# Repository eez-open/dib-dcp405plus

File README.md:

### This is a WORK IN PROGRESS!

---

### Ownership and License
The contributors are listed in CONTRIB.TXT. 

Licenses | OSHWA UID
--|--
 | 

### Overview

The EEZ DIB DCP405+ Power module is an improved version of the [DCP405](https://github.com/eez-open/modular-psu/tree/master/dcp405) module that now includes an on-board 32-bit MCU, a more accurate and faster A/D converter for simultaneous voltage and current measurement (and thus more accurate power measurement).
This version features remote current programming in addition to the existing remote voltage programming. Sense inputs are also on 4 mm safety sockets, which now enables usage of widely available (e.g. AliExpress, eBay, etc.) and affordable Kelvin cable sets (Power/Sense) usually used with LCR meters (see below)

### Feature list
- Power input: 48 Vdc (e.g. Mean Well EPP-150-48 or LRS-150F-48)
- Max. output power: 155 W (as limited with Mean Well AC/DC module capacity) 
- Voltage regulation (CV), 0 – 40 V. Voltage set resolution (_U_SET_): 16-bit, read resolution (_U_MON_): 15-bit
- Current regulation (CC) with 2-range (50 mA, 5 A). Current set resolution (_I_SET_): 16-bit, Current read resolution (_I_MON_): 20-bit for each range
- On-board low EMI switching power pre-regulator and bias power supply
- On-board OVP with full range dual crowbar (triac/MOSFET) and 20x5 mm fuse
- Down-programmer
- Output enable (OE) circuit with LED indicator combined with coupling indication
- Ø4 mm sockets (19.05 mm/0.75” pitch) for Power outputs and Sense inputs 
- Pass-thru connector for power output coupling with other power boards for e.g. doubling output voltage (up to 80 V) or current (up to 10 A)
- Remote voltage sense with LED indicator and inverse polarity protection
- Remote voltage and current programming with LED indicator (+2.5 V for full range)
- On-board 32-bit 250 MHz MCU ([STM32H503CBT6](https://www.st.com/en/microcontrollers-microprocessors/stm32h503cb.html))
- Galvanically isolated SPI bus
- I2C EEPROM for storing board specific configuration and calibration parameters
- SPI Temperature sensor
- Dimensions: 180 x 103.5 mm, 4-layer PCB
- **CE certified design**

---

This work is financed by [NLnet](https://nlnet.nl/project/BB3-CM5/) foundation

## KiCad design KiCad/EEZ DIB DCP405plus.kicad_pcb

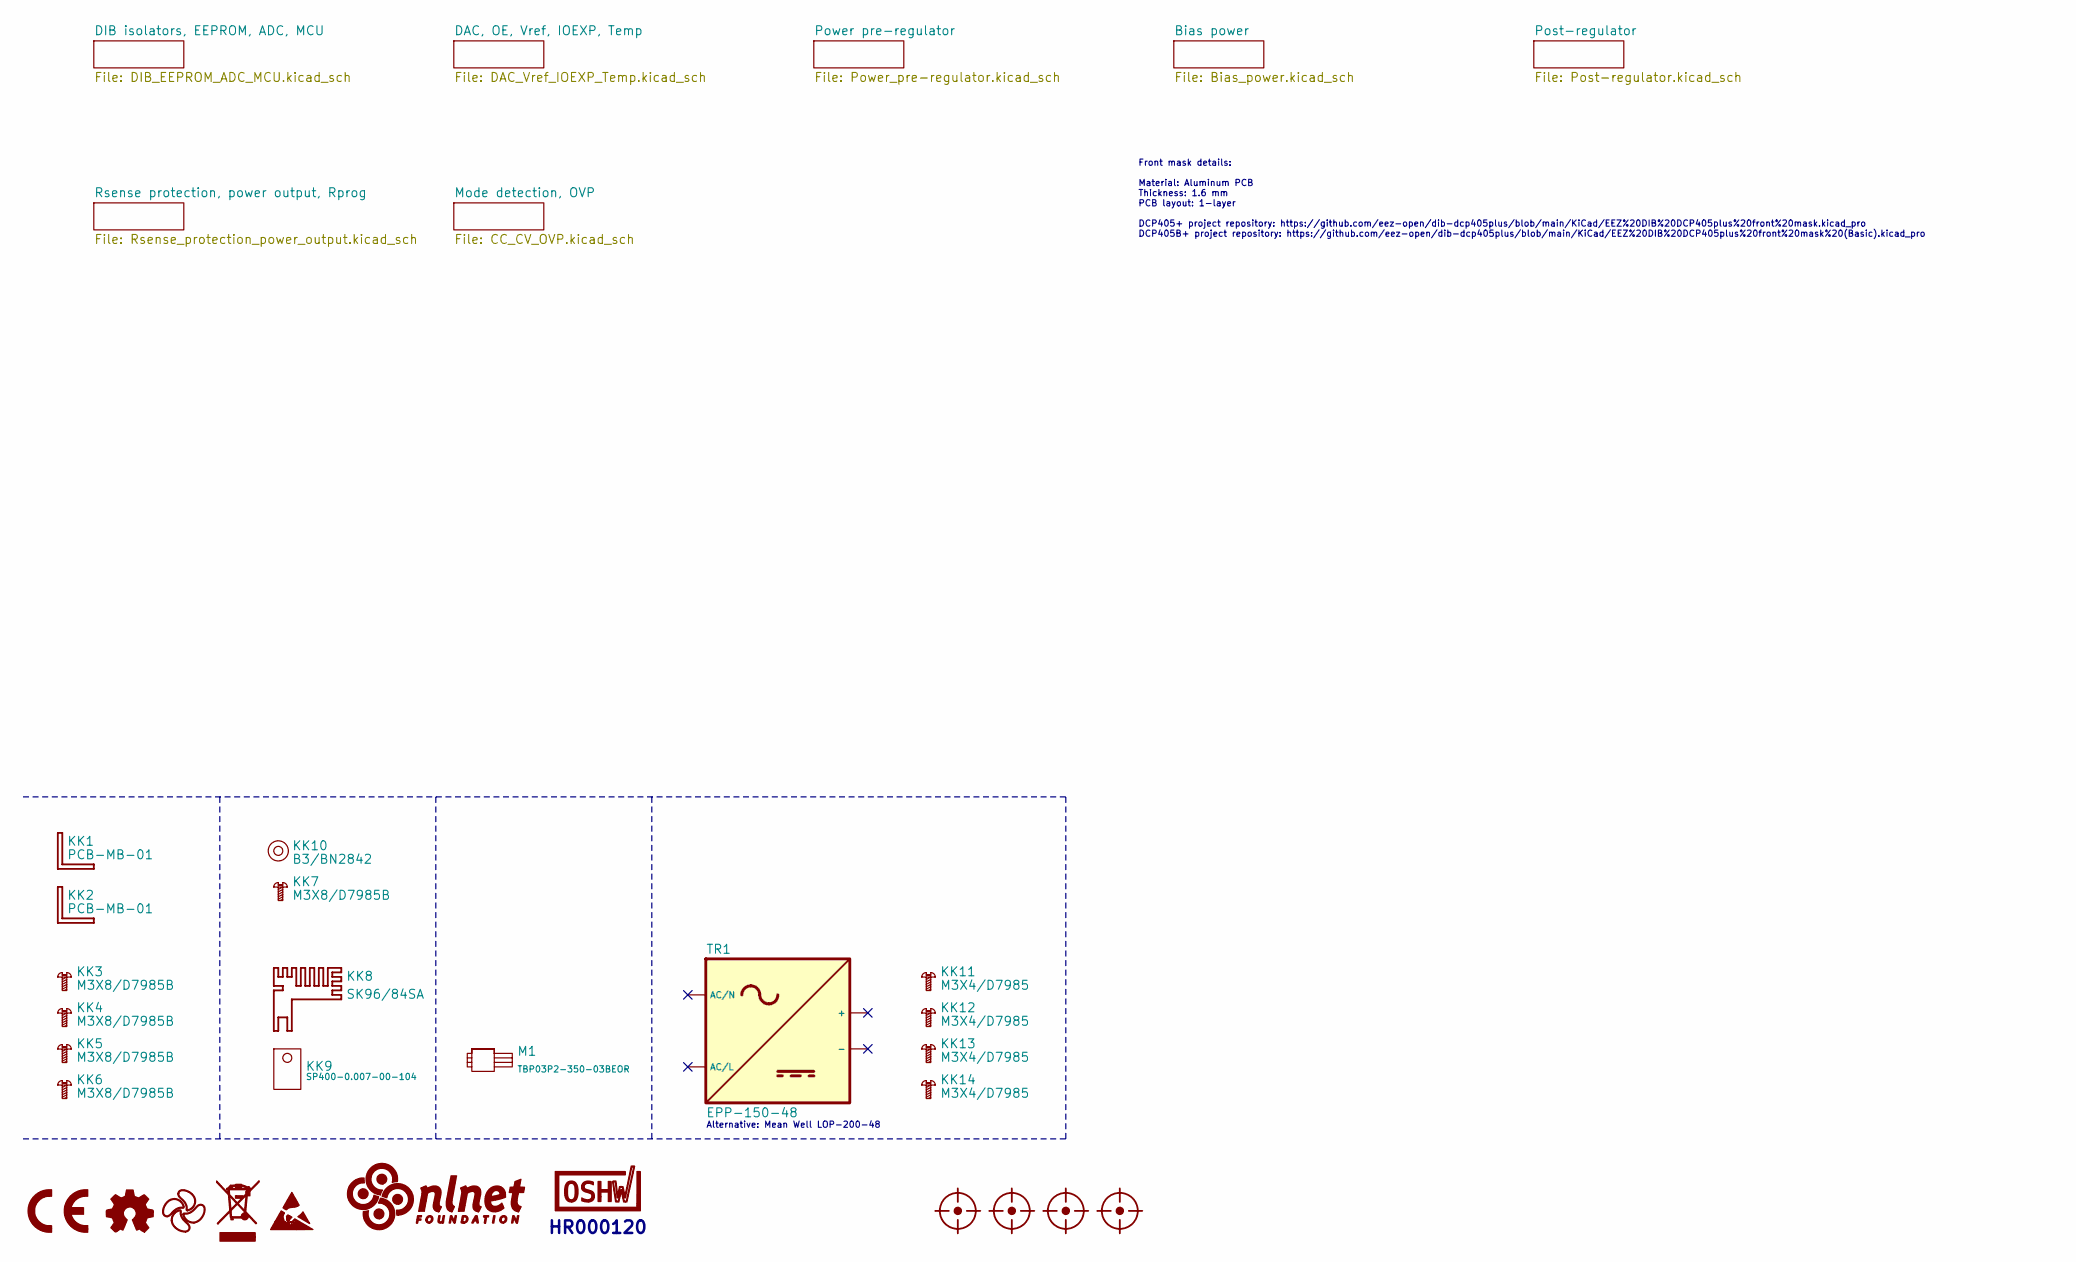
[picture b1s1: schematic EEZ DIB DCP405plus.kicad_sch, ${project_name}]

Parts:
FM1, FM2, FM3, FM4: FIDUCIAL; Fiducial_0.75mm_Mask1.5mm
KK1, KK2: PCB-MB-01; DigiKey RPC1760-ND
KK3, KK4, KK5, KK6, KK7: M3X8/D7985B
KK8: SK96/84SA; SK96_84; DigiKey 5496-SK9684SA-ND
KK9: SP400-0.007-00-104; DigiKey BER204-ND
KK10: B3/BN2842
KK11, KK12, KK13, KK14: M3X4/D7985
LOGO1: CR logo; CE logo
LOGO2: Open HW logo
LOGO3: EEZ logo; EEZ logo (outline 6mm)
LOGO4: WEEE logo
LOGO5: ESD logo
LOGO6: NLnet logo
LOGO7: OSHWA logo; OSHWA logo 6.6mm
M1: TBP03P2-350-03BEOR; DigiKey 2223-TBP03P2-350-03BEOR-ND
TR1: EPP-150-48; DigiKey 1866-LOP-200-48-ND

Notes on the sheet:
Alternative: Mean Well LOP-200-48
HR000120
Front mask details: Material: Aluminum PCB Thickness: 1.6 mm PCB layout: 1-layer DCP405+ project repository: https://github.com/eez-open/dib-dcp405plus/blob/main/KiCad/EEZ%20DIB%20DCP405plus%20front%20mask.kicad_pro DCP405B+ project repository: https://github.com/eez-open/dib-dcp405plus/blob/main/K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

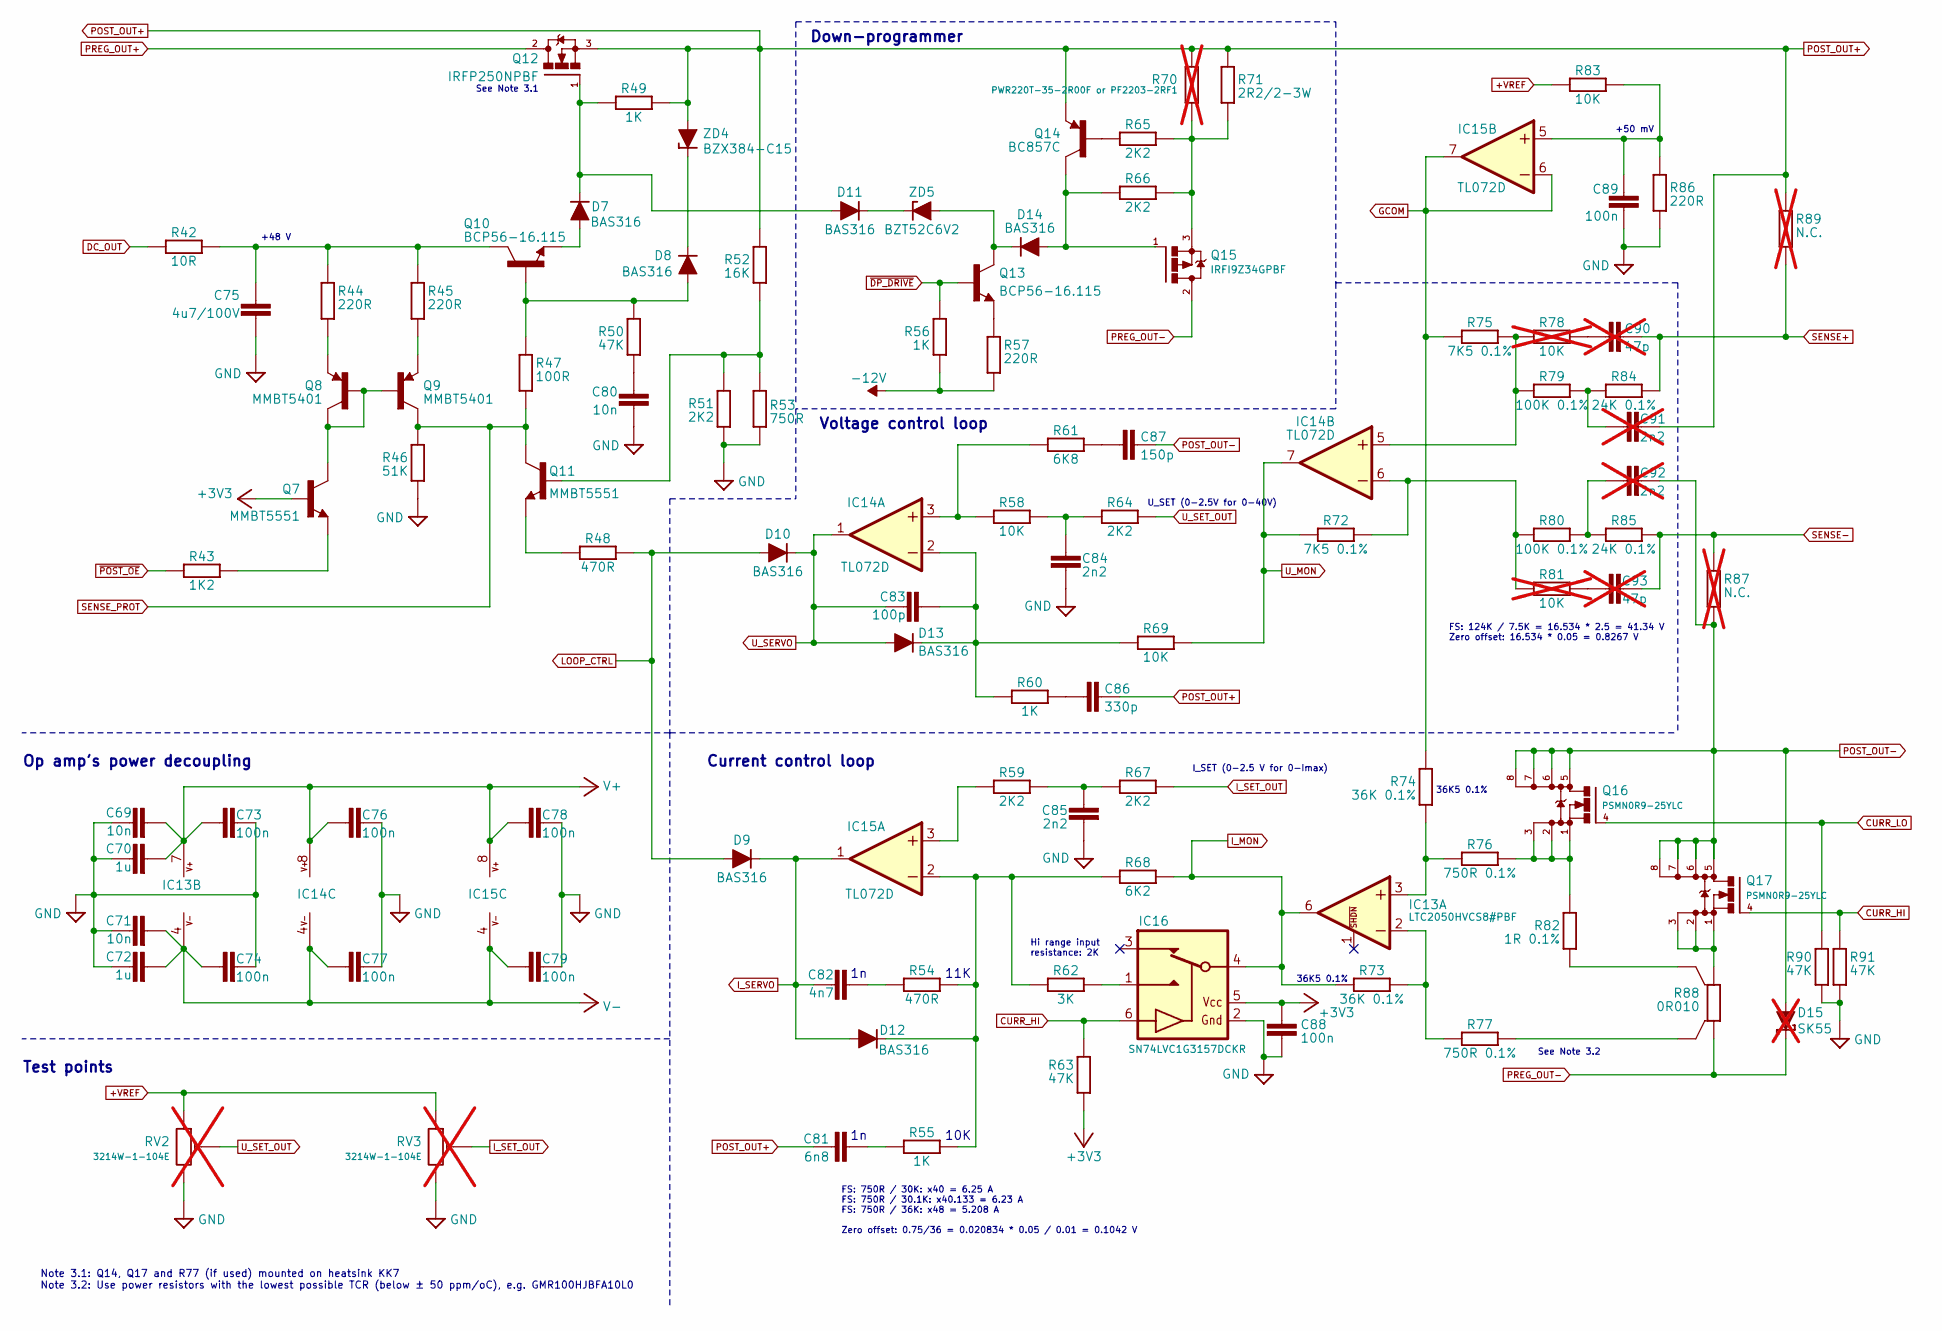
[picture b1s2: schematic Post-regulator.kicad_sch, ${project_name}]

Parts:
C69, C71, C80: 10n; C_0805_2012Metric; DigiKey 490-7194-1-ND
C70, C72: 1u; C_0805_2012Metric; DigiKey 1276-2931-1-ND
C73, C74, C76, C77, C78, C79, C88, C89: 100n; C_0603_1608Metric; DigiKey 1276-6717-1-ND
C75: 4u7/100V; C_1210_3225Metric; DigiKey 587-5034-1-ND
C81: 6n8; C_0805_2012Metric; DigiKey 399-C0805C682K5RACTUCT-ND
C82: 4n7; C_0805_2012Metric; DigiKey 732-12255-1-ND
C83: 100p; C_0805_2012Metric; DigiKey 399-15000-1-ND
C84, C85: 2n2; C_0805_2012Metric; DigiKey 1276-2478-1-ND
C86: 330p; C_0805_2012Metric; DigiKey 311-1117-1-ND
C87: 150p; C_0805_2012Metric; DigiKey 732-7853-1-ND
C90, C93: 47p; C_0805_2012Metric; not fitted
C91, C92: 2n2; C_0805_2012Metric; DigiKey 399-C0805C222K5RAC7210TR-ND; not fitted
D7, D8, D9, D10, D11, D12, D13, D14: BAS316; SOD-323_1P8X1P35_ONS-M; DigiKey 5399-BAS316CT-ND
D15: SK55; DO214AA; DigiKey SK56A-LTPMSCT-ND; not fitted
IC13: LTC2050HVCS8#PBF; SOIC127P600X173-8N; DigiKey LTC2050HVCS8#TRPBFCT-ND
IC14, IC15: TL072D; SOIC127P600X173-8N; DigiKey 296-1282-1-ND
IC16: SN74LVC1G3157DCKR; SOT65P210X110-6N; DigiKey 296-14909-1-ND
Q7, Q11: MMBT5551; SOT23-BEC; DigiKey MMBT5551LT1GOSCT-ND
Q8, Q9: MMBT5401; SOT23-BEC; DigiKey MMBT5401-FDICT-ND
Q10, Q13: BCP56-16.115; SOT223-BCE; DigiKey 5399-BCP56-16CT-ND
Q12: IRFP250NPBF; TO247-3_SUNKEN; DigiKey IRFP250PBF-ND
Q14: BC857C; SOT23-BEC; DigiKey 4878-BC857CCT-ND
Q15: IRFI9Z34GPBF; TO220FP-V; DigiKey IRFI9Z34GPBF-ND
Q16, Q17: PSMN0R9-25YLC; TDSON-8; DigiKey 1727-5292-1-ND
R42: 10R; R_0805_2012Metric; DigiKey 311-10.0CRCT-ND
R43: 1K2; R_0805_2012Metric; DigiKey 311-1.20KCRCT-ND
R44, R45, R57, R86: 220R; R_0805_2012Metric; DigiKey RMCF0805FT220RCT-ND
R46: 51K; R_0805_2012Metric; DigiKey 311-51.0KCRCT-ND
R47: 100R; R_0603_1608Metric; DigiKey 13-RC0603FR-10100RLCT-ND
R48, R54: 470R; R_0805_2012Metric; DigiKey 13-RC0805FR-13470RLCT-ND
R49, R55, R56, R60: 1K; R_0805_2012Metric; DigiKey 311-1.00KCRCT-ND
R50, R63, R90, R91: 47K; R_0805_2012Metric; DigiKey RHM47KKCT-ND
R51, R59, R64, R65, R66, R67: 2K2; R_0805_2012Metric; DigiKey 311-2.20KCRCT-ND
R52: 16K; R_0805_2012Metric; DigiKey 311-16.0KCRCT-ND
R53: 750R; R_0805_2012Metric; DigiKey A126385CT-ND
R58, R69, R83: 10K; R_0805_2012Metric; DigiKey 311-10.0KCRCT-ND
R61: 6K8; R_0805_2012Metric; DigiKey 311-6.80KCRCT-ND
R62: 3K; R_0603_1608Metric; DigiKey 311-3.00KCRCT-ND
R68: 6K2; R_0805_2012Metric; DigiKey 311-6.20KCRCT-ND
R70: PWR220T-35-2R00F or PF2203-2RF1; TO220-2-V; DigiKey 696-1313-ND; not fitted
R71: 2R2/2-3W; R_2512_6332Metric; DigiKey CRM2512-JW-2R2ELFCT-ND
R72, R75: 7K5 0.1%; R_0805_2012Metric; DigiKey YAG1974CT-ND
R73, R74: 36K 0.1%; R_0805_2012Metric; DigiKey YAG4886CT-ND
R76, R77: 750R 0.1%; R_0805_2012Metric; DigiKey YAG4940CT-ND
R78, R81: 10K; R_0805_2012Metric; not fitted
R79, R80: 100K 0.1%; R_0805_2012Metric; DigiKey YAG4808CT-ND
R82: 1R 0.1%; R_1206_3216Metric; DigiKey 1712-CPF1206B1R0E1CT-ND
R84, R85: 24K 0.1%; R_0805_2012Metric; DigiKey P24KBFCT-ND
R87, R89: N.C.; R_0805_2012Metric; not fitted
R88: 0R010; R_2512-4WIRE; DigiKey 846-GMR100HJBFA10L0CT-ND
RV2, RV3: 3214W-1-104E; TRIM_3214W-1-104E; DigiKey 3214W-104ECT-ND; not fitted
ZD4: BZX384-C15; SOD-323_1P8X1P35_ONS-M; DigiKey 1727-BZX384-C15-QFCT-ND
ZD5: BZT52C6V2; SOD123; DigiKey 4878-BZT52C6V2CT-ND

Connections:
+3V3: C88.1, IC16.5 (VDD), Q7.B, R63.1; also elsewhere on the board
+VREF: R83.1, RV2.1, RV3.1; also elsewhere on the board
-12V: R56.2, R57.2; also elsewhere on the board
CURR_HI: IC16.6 (CTRL), Q17.4 (G), R63.2, R91.2; also elsewhere on the board
CURR_LO: Q16.4 (G), R90.2; also elsewhere on the board
DC_OUT: R42.2; also elsewhere on the board
GCOM: IC15.6 (-IN), IC15.7 (OUT), R74.1, R75.1; also elsewhere on the board
GND: C69.1, C70.1, C71.1, C72.1, C73.2, C74.2, C75.2, C76.1, C77.1, C78.1, C79.1, C80.2, C84.2, C85.2, C88.2, C89.2, IC16.2 (GND), R46.1, R51.1, R53.1, R86.2, R90.1, R91.1, RV2.3, RV3.3; also elsewhere on the board
I_MON: IC13.6 (OUT), IC16.4 (COM), R68.1, R73.2; also elsewhere on the board
I_SERVO: C82.2, D9.C, D12.A, IC15.1 (OUT); also elsewhere on the board
I_SET_OUT: R67.1, RV3.2; also elsewhere on the board
LOOP_CTRL: D9.A, D10.A, R48.1; also elsewhere on the board
unnamed: C75.1, Q10.C, R42.1, R44.2, R45.2
unnamed: C80.1, R50.1
unnamed: C81.2, R55.1
unnamed: C82.1, R54.1
unnamed: C84.1, R58.1, R64.2
unnamed: C85.1, R59.1, R67.2
unnamed: C86.2, R60.1
unnamed: C87.2, R61.1
unnamed: C90.2, R78.1
unnamed: C91.1, R79.2, R84.1
unnamed: C92.1, R80.2, R85.1
unnamed: C93.2, R81.1
unnamed: D7.A, Q10.E
unnamed: D8.A, Q10.B, R47.1, R50.2
unnamed: D8.C, ZD4.C
unnamed: D11.C, ZD5.C
unnamed: D14.C, Q13.C, ZD5.A
unnamed: IC13.3 (+IN), R74.2, R76.2
unnamed: IC13.2 (-IN), R73.1, R77.2
unnamed: IC14.3 (+IN), R58.2, R61.2
unnamed: C83.1, D13.C, IC14.2 (-IN), R60.2, R69.2
unnamed: IC14.5 (+IN), R75.2, R78.2, R79.1
unnamed: IC14.6 (-IN), R72.2, R80.1, R81.2
unnamed: IC15.3 (+IN), R59.2
unnamed: D12.C, IC15.2 (-IN), R54.2, R55.2, R62.2, R68.2
unnamed: C89.1, IC15.5 (+IN), R83.2, R86.1
unnamed: IC16.1 (NO), R62.1
unnamed: Q7.C, Q8.B, Q8.C, Q9.B
unnamed: Q7.E, R43.2
unnamed: Q8.E, R44.1
unnamed: Q9.E, R45.1
unnamed: Q11.B, R51.2, R52.1, R53.2
unnamed: Q11.E, R48.2
unnamed: D7.C, D11.A, Q12.1 (G), R49.1
unnamed: Q13.E, R57.1
unnamed: Q14.B, R65.2
unnamed: D14.A, Q14.C, Q15.1 (G), R66.2
unnamed: Q15.3 (S), R65.1, R66.1, R70.1, R71.2
unnamed: Q16.1 (S), Q16.2 (S), Q16.3 (S), R76.1, R82.2
unnamed: Q17.1 (S), Q17.2 (S), Q17.3 (S), R88.2
unnamed: R77.1, R88.1S
unnamed: R82.1, R88.2S
POST_OUT+: C81.1, C86.1, C91.2, Q12.3 (S), Q14.E, R49.2, R52.2, R70.2, R71.1, R89.1, ZD4.A; also elsewhere on the board
POST_OUT-: C87.1, C92.2, D15.A, Q16.5 (D), Q16.6 (S), Q16.7 (S), Q16.8 (S), Q17.5 (D), Q17.6 (S), Q17.7 (S), Q17.8 (S), R87.2; also elsewhere on the board
PREG_OUT+: Q12.2 (D); also elsewhere on the board
PREG_OUT-: D15.C, Q15.2 (D), R88.1; also elsewhere on the board
SENSE+: C90.1, R84.2, R89.2; also elsewhere on the board
SENSE-: C93.1, R85.2, R87.1; also elsewhere on the board
SENSE_PROT: Q9.C, Q11.C, R46.2, R47.2; also elsewhere on the board
U_MON: IC14.7 (OUT), R69.1, R72.1; also elsewhere on the board
U_SERVO: C83.2, D10.C, D13.A, IC14.1 (OUT); also elsewhere on the board
U_SET_OUT: R64.1, RV2.2; also elsewhere on the board
V+: C69.2, C70.2, C73.1, C76.2, C78.2, IC13.7 (V+), IC14.8 (V+), IC15.8 (V+); also elsewhere on the board
V-: C71.2, C72.2, C74.1, C77.2, C79.2, IC13.4 (V-), IC14.4 (V-), IC15.4 (V-); also elsewhere on the board
~DP_DRIVE: Q13.B, R56.1; also elsewhere on the board
~POST_OE: R43.1; also elsewhere on the board

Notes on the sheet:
Hi range input resistance: 2K
FS: 124K / 7.5K = 16.534 * 2.5 = 41.34 V Zero offset: 16.534 * 0.05 = 0.8267 V
11K
Down-programmer
+50 mV
I_SET (0-2.5 V for 0-Imax)
Op amp's power decoupling
See Note 3.1
36K5 0.1%
10K
Current control loop
Voltage control loop
See Note 3.2
+48 V
U_SET (0-2.5V for 0-40V)
Test points
FS: 750R / 30K: x40 = 6.25 A FS: 750R / 30.1K: x40.133 = 6.23 A FS: 750R / 36K: x48 = 5.208 A Zero offset: 0.75/36 = 0.020834 * 0.05 / 0.01 = 0.1042 V
Note 3.1: Q14, Q17 and R77 (if used) mounted on heatsink KK7 Note 3.2: Use power resistors with the lowest possible TCR (below ± 50 ppm/oC), e.g. GMR100HJBFA10L0

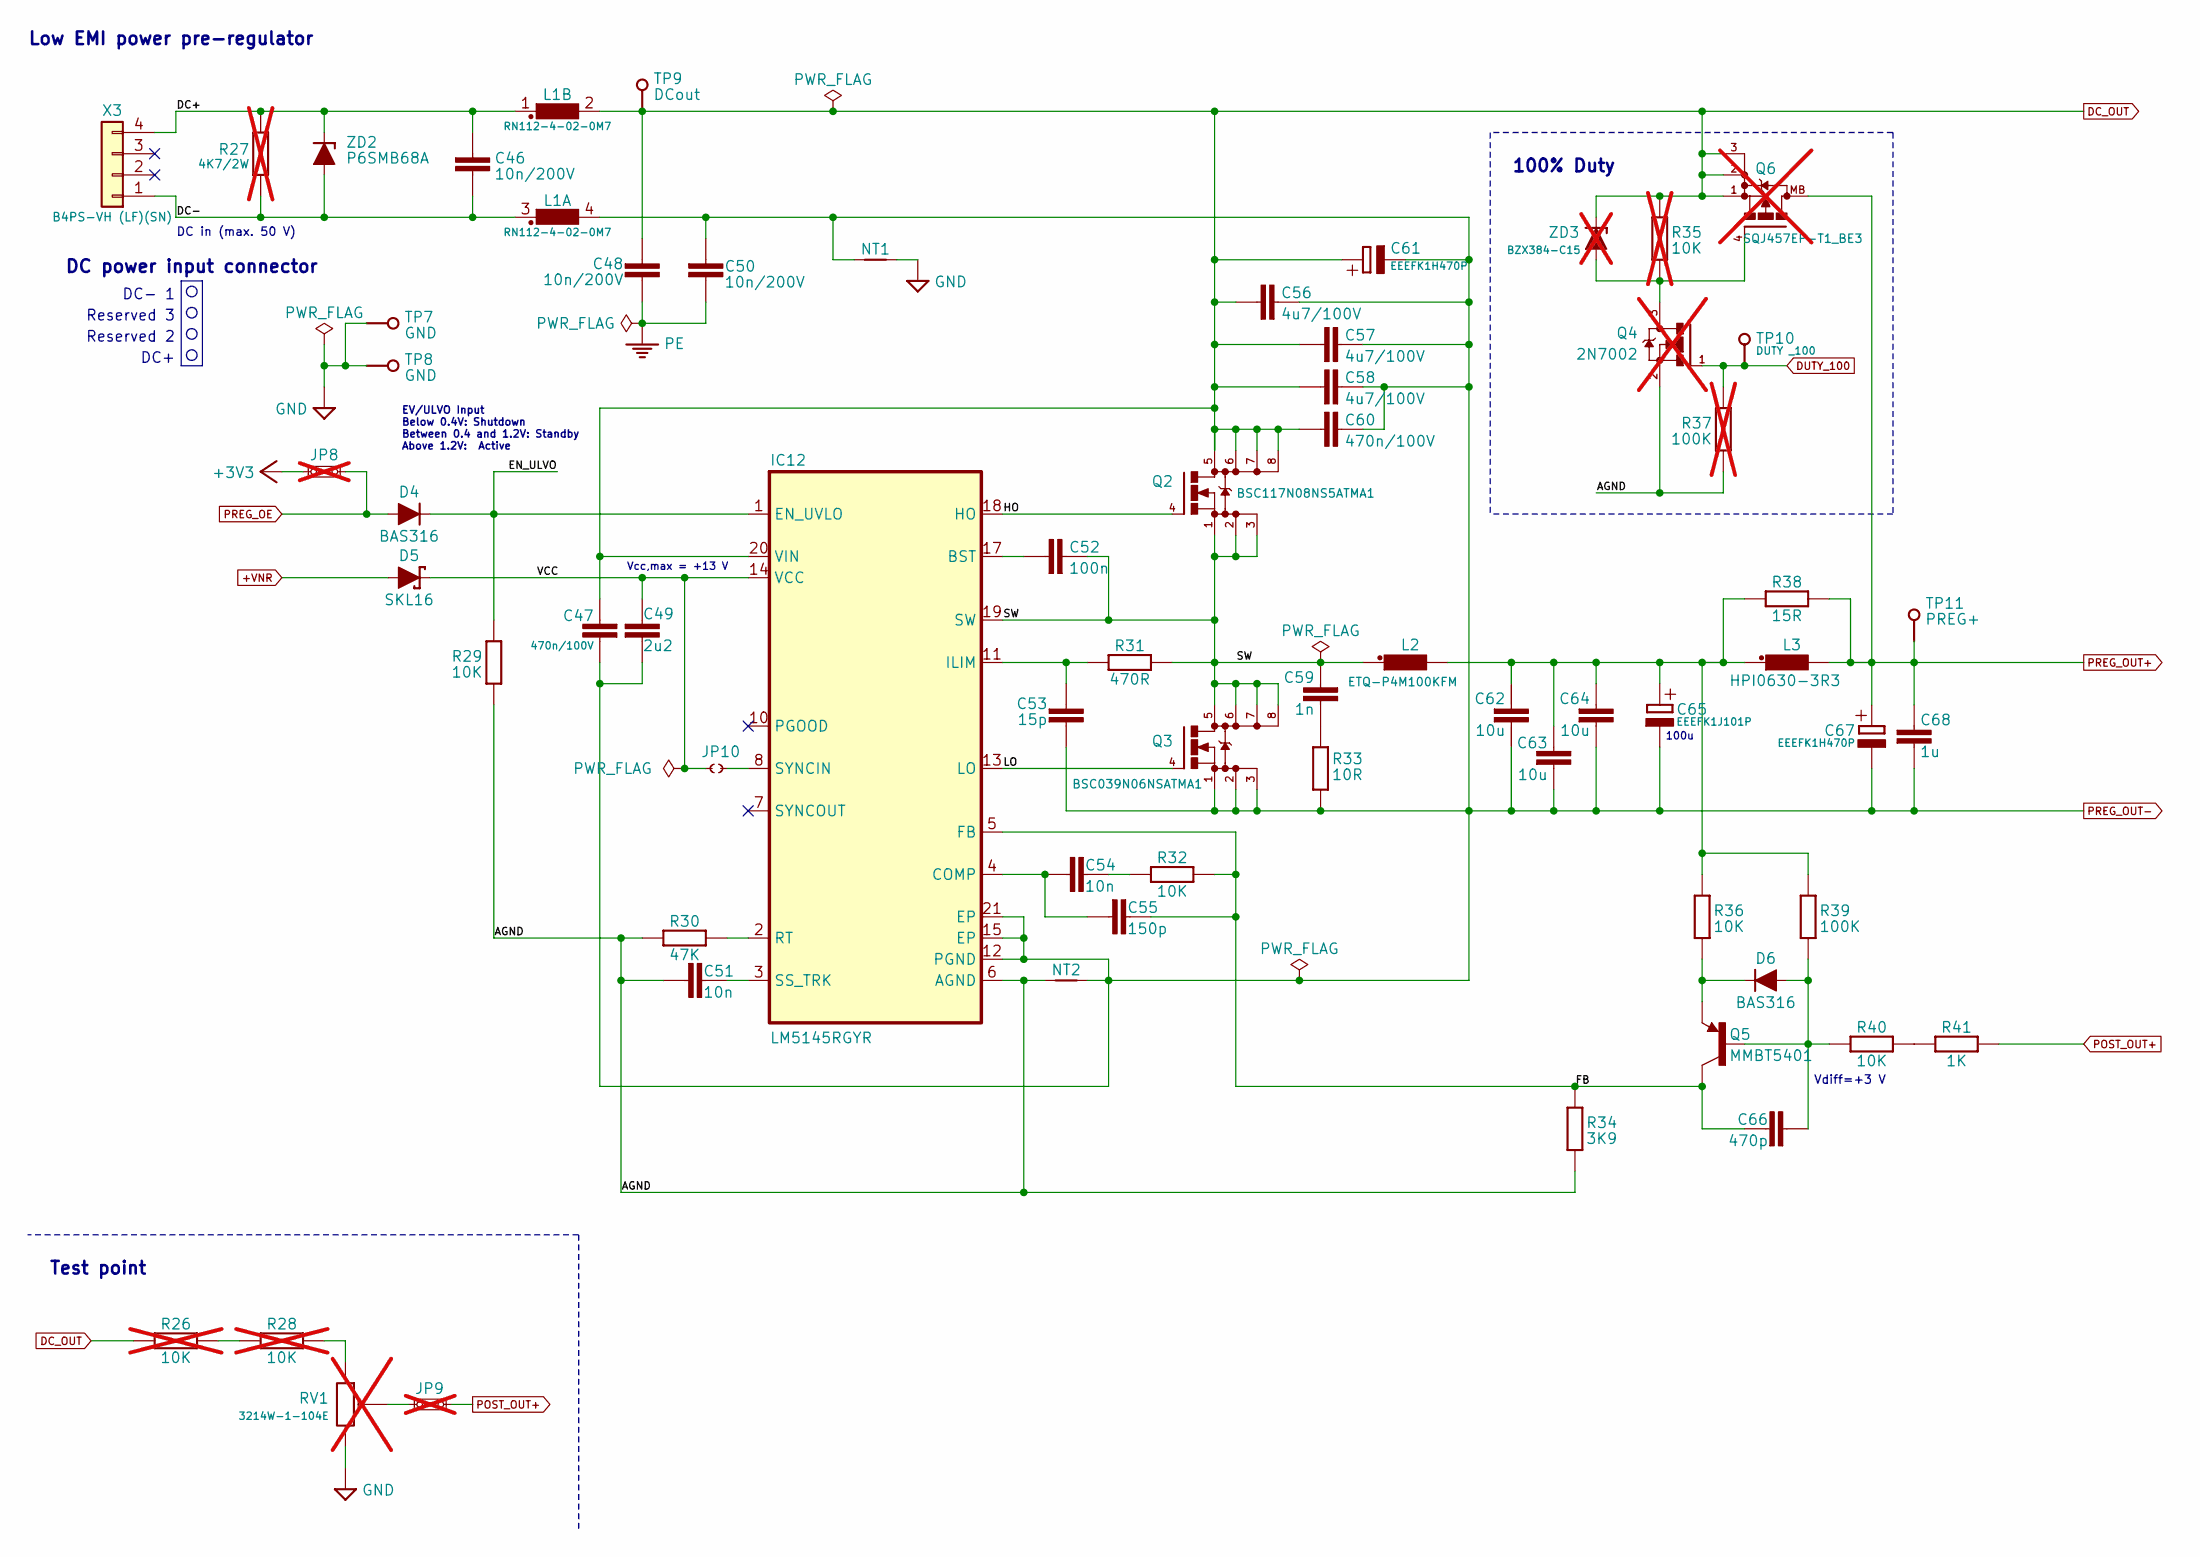
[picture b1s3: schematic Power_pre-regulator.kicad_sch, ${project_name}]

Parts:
C46, C48, C50: 10n/200V; C_1206_3216Metric; DigiKey 311-4491-1-ND
C47, C60: 470n/100V; C_0805_2012Metric; DigiKey 587-5014-1-ND
C49: 2u2; C_1206_3216Metric; DigiKey 1276-3138-1-ND
C51, C54: 10n; C_0805_2012Metric; DigiKey 490-7194-1-ND
C52: 100n; C_0603_1608Metric; DigiKey 1276-6717-1-ND
C53: 15p; C_0603_1608Metric; DigiKey 732-7847-1-ND
C55: 150p; C_0805_2012Metric; DigiKey 732-7853-1-ND
C56, C57, C58: 4u7/100V; C_1210_3225Metric; DigiKey 587-5034-1-ND
C59: 1n; C_0603_1608Metric; DigiKey 1276-1018-1-ND
C61, C67: EEEFK1H470P; CAPAE830X1050N; DigiKey PCE3815CT-ND
C62, C63, C64: 10u; C_1210_3225Metric; DigiKey 1276-3387-1-ND
C65: EEEFK1J101P; CAPAE1030X1050N; DigiKey PCE3819CT-ND
C66: 470p; C_0805_2012Metric; DigiKey 732-7837-1-ND
C68: 1u; C_0805_2012Metric; DigiKey 1276-2931-1-ND
D4, D6: BAS316; SOD-323_1P8X1P35_ONS-M; DigiKey 5399-BAS316CT-ND
D5: SKL16; SOD123; DigiKey RB160MM-60CT-ND
IC12: LM5145RGYR; RGY0020B; DigiKey 296-47121-1-ND
JP8, JP9: M22-2010246; DigiKey M22-2010346-ND; not fitted
JP10: JP2-CUT-0805; JP2 open (0603)
L1: RN112-4-02-0M7; RN112; DigiKey 817-2100-ND
L2: ETQ-P4M100KFM; PANASONIC_ETQ-P4_KFM; DigiKey P124167CT-ND
L3: HPI0630-3R3; COILCRAFT_HPI0630; DigiKey 445-180834-1-ND
NT1: NetTie_2; NetTie-2_SMD_Pad1.5mm
NT2: NetTie_2; NetTie-2_SMD_Pad0.2mm
Q2: BSC117N08NS5ATMA1; TDSON-8; DigiKey BSC117N08NS5ATMA1CT-ND
Q3: BSC039N06NSATMA1; TDSON-8; DigiKey BSC039N06NSATMA1CT-ND
Q4: 2N7002; SOT103P240X110-3N; DigiKey T2N7002AKLMCT-ND; not fitted
Q5: MMBT5401; SOT23-BEC; DigiKey MMBT5401-FDICT-ND
Q6: SQJ457EP-T1_BE3; PowerPAK SO-8; DigiKey 742-SQJ457EP-T1_BE3CT-ND; not fitted
R26, R28, R35: 10K; R_0805_2012Metric; DigiKey 311-10.0KCRCT-ND; not fitted
R27: 4K7/2W; R_2512_6332Metric; not fitted
R29, R32, R36, R40: 10K; R_0805_2012Metric; DigiKey 311-10.0KCRCT-ND
R30: 47K; R_0805_2012Metric; DigiKey RHM47KKCT-ND
R31: 470R; R_0805_2012Metric; DigiKey 13-RC0805FR-13470RLCT-ND
R33: 10R; R_0805_2012Metric; DigiKey 311-10.0CRCT-ND
R34: 3K9; R_0805_2012Metric; DigiKey A126369CT-ND
R37: 100K; R_0805_2012Metric; DigiKey RMCF0805FT100KCT-ND; not fitted
R38: 15R; R_2010_5025Metric; DigiKey A129910CT-ND
R39: 100K; R_0805_2012Metric; DigiKey RMCF0805FT100KCT-ND
R41: 1K; R_0805_2012Metric; DigiKey 311-1.00KCRCT-ND
RV1: 3214W-1-104E; TRIM_3214W-1-104E; DigiKey 3214W-104ECT-ND; not fitted
TP7, TP8: PCB_TEST_TABSHIELD; Testhole 24_50mils
TP9, TP10, TP11: TEST-PIN_0.9MM; Testhole 24_50mils
X3: B4PS-VH (LF)(SN); B4PS-VH; DigiKey 455-B4PS-VH-ND
ZD2: P6SMB68A; DO214AA; DigiKey P6SMB68ABBCT-ND
ZD3: BZX384-C15; SOD-323_1P8X1P35_ONS-M; DigiKey 1727-4986-1-ND; not fitted

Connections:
+3V3: JP8.1; also elsewhere on the board
+VNR: D5.A; also elsewhere on the board
/Power pre-regulator/AGND: C51.2, IC12.6 (AGND), NT2.1, Q4.2 (S), R29.1, R30.1, R34.2, R37.2
/Power pre-regulator/DC+: C46.2, L1.1, R27.1, X3.4, ZD2.C
/Power pre-regulator/DC-: C46.1, L1.3 (1), R27.2, X3.1, ZD2.A
/Power pre-regulator/EN_ULVO: D4.C, IC12.1 (EN_UVLO), R29.2
/Power pre-regulator/FB: C55.1, C66.1, IC12.5 (FB), Q5.C, R32.2, R34.1
/Power pre-regulator/HO: IC12.18 (HO), Q2.4 (G)
/Power pre-regulator/LO: IC12.13 (LO), Q3.4 (G)
/Power pre-regulator/SW: C52.2, C59.1, IC12.19 (SW), L2.1, Q2.1 (S), Q2.2 (S), Q2.3 (S), Q3.5 (D), Q3.6 (S), Q3.7 (S), Q3.8 (S), R31.2
/Power pre-regulator/VCC: C49.2, D5.C, IC12.14 (VCC), JP10.1
DC_OUT: C47.2, C48.2, C56.1, C57.1, C58.1, C60.2, C61.+, IC12.20 (VIN), L1.2, Q2.5 (D), Q2.6 (S), Q2.7 (S), Q2.8 (S), Q6.1 (S), Q6.2 (S), Q6.3 (S), R26.2, R35.2, TP9.1 (P$1_1), ZD3.C; also elsewhere on the board
DUTY_100: Q4.1 (G), R37.1, TP10.1 (P$1_1); also elsewhere on the board
GND: NT1.2, RV1.3, TP7.1 (P$1_1), TP8.1 (P$1_1); also elsewhere on the board
unnamed: C54.1, R32.1
unnamed: C59.2, R33.2
unnamed: C62.1, C63.1, C64.1, C65.+, L2.2, L3.1, R36.1, R38.2, R39.1
unnamed: C66.2, D6.A, Q5.B, R39.2, R40.1
unnamed: D6.C, Q5.E, R36.2
unnamed: C52.1, IC12.17 (BST)
unnamed: C54.2, C55.2, IC12.4 (COMP)
unnamed: C53.1, IC12.11 (ILIM), R31.1
unnamed: IC12.2 (RT), R30.2
unnamed: C51.1, IC12.3 (SS_TRK)
unnamed: IC12.8 (SYNCIN), JP10.2
unnamed: JP9.1, RV1.2
unnamed: Q4.3 (D), Q6.4 (G), R35.1, ZD3.A
unnamed: R26.1, R28.2
unnamed: R28.1, RV1.1
unnamed: R40.2, R41.1
PE: C48.1, C50.2; also elsewhere on the board
POST_OUT+: JP9.2, R41.2; also elsewhere on the board
PREG_OE: D4.A, JP8.2; also elsewhere on the board
PREG_OUT+: C67.+, C68.2, L3.2, Q6.MB, R38.1, TP11.1 (P$1_1); also elsewhere on the board
PREG_OUT-: C47.1, C49.1, C50.1, C53.2, C56.2, C57.2, C58.2, C60.1, C61.-, C62.2, C63.2, C64.2, C65.-, C67.-, C68.1, IC12.12 (PGND), IC12.15 (EP), IC12.21 (EP), L1.4 (2), NT1.1, NT2.2, Q3.1 (S), Q3.2 (S), Q3.3 (S), R33.1; also elsewhere on the board

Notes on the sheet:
DC- 1
Reserved 2
Low EMI power pre-regulator
DC+
Vcc,max = +13 V
Reserved 3
DC in (max. 50 V)
100% Duty
Vdiff=+3 V
Test point
DC power input connector
100u
EV/ULVO Input Below 0.4V: Shutdown Between 0.4 and 1.2V: Standby Above 1.2V: Active

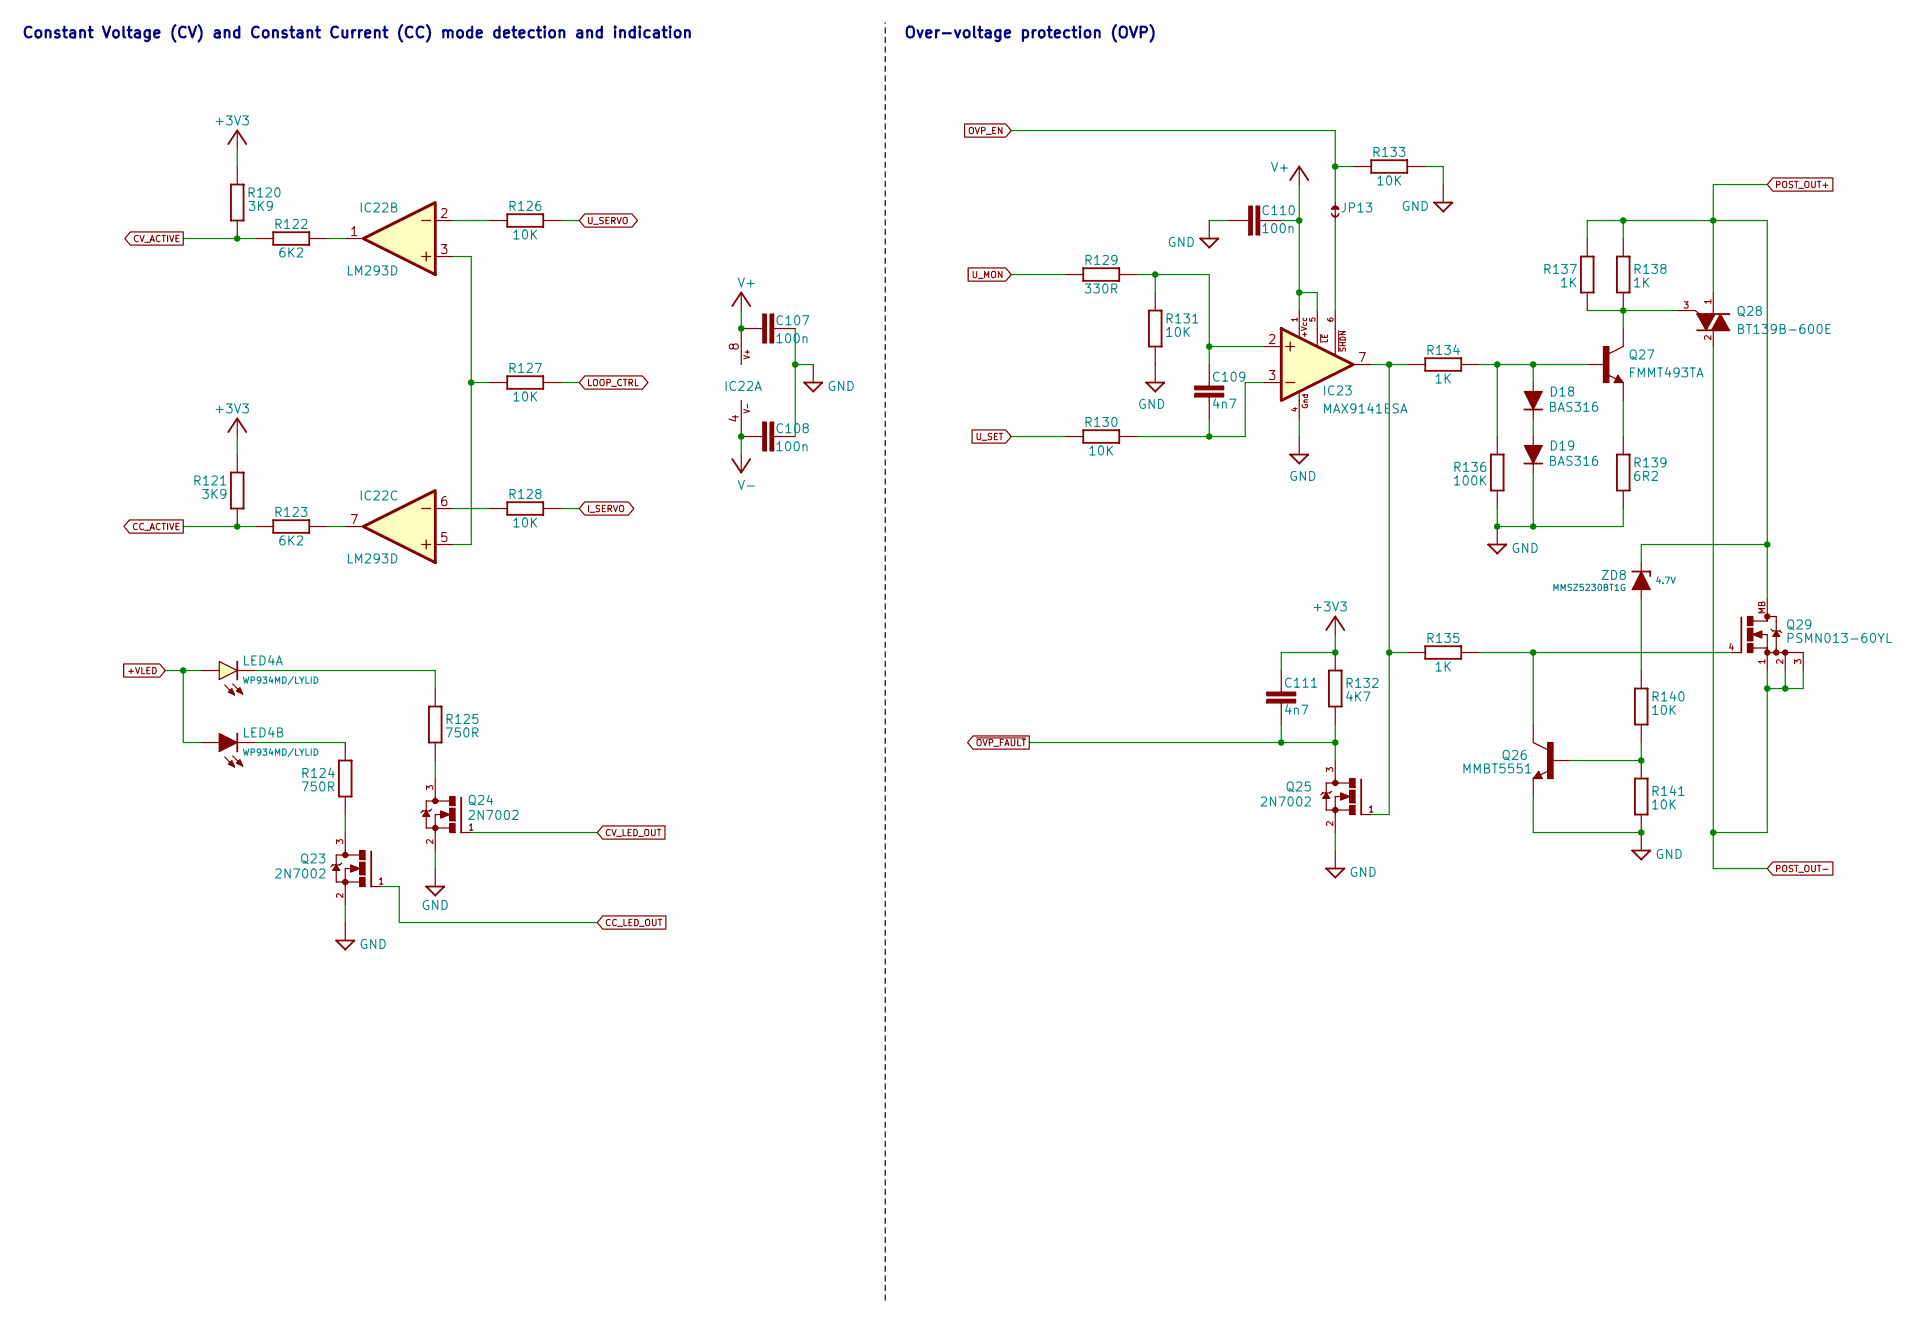
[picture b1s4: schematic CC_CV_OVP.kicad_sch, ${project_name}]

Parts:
C107, C108, C110: 100n; C_0603_1608Metric; DigiKey 1276-6717-1-ND
C109, C111: 4n7; C_0805_2012Metric; DigiKey 732-12255-1-ND
D18, D19: BAS316; SOD-323_1P8X1P35_ONS-M; DigiKey 5399-BAS316CT-ND
IC22: LM293D; SOIC127P600X173-8N; DigiKey LM293DR2GOSCT-ND
IC23: MAX9141ESA; SOIC127P600X173-8N; DigiKey MAX9141ESA+-ND
JP13: JP2-NOCUT-0805; JP2 shorted (0603)
LED4: WP934MD/LYLID; WP934MD_2YD; DigiKey 350-2716-ND
Q23, Q24, Q25: 2N7002; SOT103P240X110-3N; DigiKey T2N7002AKLMCT-ND
Q26: MMBT5551; SOT23-BEC; DigiKey MMBT5551LT1GOSCT-ND
Q27: FMMT493TA; SOT23-BEC; DigiKey FMMT493CT-ND
Q28: BT139B-600E; TO-263_SOT-404; DigiKey 1740-1290-1-ND
Q29: PSMN013-60YL; SOT669; DigiKey 1727-2589-1-ND
R120, R121: 3K9; R_0805_2012Metric; DigiKey A126369CT-ND
R122, R123: 6K2; R_0805_2012Metric; DigiKey 311-6.20KCRCT-ND
R124, R125: 750R; R_0805_2012Metric; DigiKey A126385CT-ND
R126, R127, R128, R130, R131, R133, R140, R141: 10K; R_0805_2012Metric; DigiKey 311-10.0KCRCT-ND
R129: 330R; R_0805_2012Metric; DigiKey A129743CT-ND
R132: 4K7; R_0805_2012Metric; DigiKey 311-4.70KCRCT-ND
R134, R135, R137, R138: 1K; R_0805_2012Metric; DigiKey 311-1.00KCRCT-ND
R136: 100K; R_0805_2012Metric; DigiKey RMCF0805FT100KCT-ND
R139: 6R2; R_0805_2012Metric; DigiKey 311-6.20CRCT-ND
ZD8: MMSZ5230BT1G; SOD123; DigiKey MMSZ4V7T1GOSCT-ND

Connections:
+3V3: C111.1, R120.2, R121.2, R132.1; also elsewhere on the board
+VLED: LED4.BA (A), LED4.TA (A); also elsewhere on the board
CC_ACTIVE: R121.1, R123.2; also elsewhere on the board
CC_LED_OUT: Q23.1 (G); also elsewhere on the board
CV_ACTIVE: R120.1, R122.2; also elsewhere on the board
CV_LED_OUT: Q24.1 (G); also elsewhere on the board
GND: C107.1, C108.1, C110.1, D19.C, IC23.4 (GND), Q23.2 (S), Q24.2 (S), Q25.2 (S), Q26.E, R131.2, R133.1, R136.1, R139.1, R141.1; also elsewhere on the board
I_SERVO: R128.1; also elsewhere on the board
LOOP_CTRL: R127.2; also elsewhere on the board
unnamed: D18.A, Q27.B, R134.1, R136.2
unnamed: D18.C, D19.A
unnamed: IC22.3 (+IN), IC22.5 (+IN), R127.1
unnamed: IC22.2 (-IN), R126.2
unnamed: IC22.1 (OUT), R122.1
unnamed: IC22.6 (-IN), R128.2
unnamed: IC22.7 (OUT), R123.1
unnamed: C109.1, IC23.2 (+IN), R129.2, R131.1
unnamed: C109.2, IC23.3 (-IN), R130.2
unnamed: IC23.7 (OUT), Q25.1 (G), R134.2, R135.2
unnamed: IC23.6 (~SHDN), JP13.2
unnamed: LED4.TC (C), R125.1
unnamed: LED4.BC (C), R124.2
unnamed: Q23.3 (D), R124.1
unnamed: Q24.3 (D), R125.2
unnamed: Q26.B, R140.1, R141.2
unnamed: Q27.E, R139.2
unnamed: Q27.C, Q28.3 (G), R137.1, R138.1
unnamed: Q26.C, Q29.4 (G), R135.1
unnamed: R140.2, ZD8.A
OVP_EN: JP13.1, R133.2; also elsewhere on the board
POST_OUT+: Q28.1 (A1), Q29.MB, R137.2, R138.2, ZD8.C; also elsewhere on the board
POST_OUT-: Q28.2 (A2), Q29.1 (S), Q29.2 (S), Q29.3 (S); also elsewhere on the board
U_MON: R129.1; also elsewhere on the board
U_SERVO: R126.1; also elsewhere on the board
U_SET: R130.1; also elsewhere on the board
V+: C107.2, C110.2, IC22.8 (V+), IC23.1 (+VCC), IC23.5 (~LE); also elsewhere on the board
V-: C108.2, IC22.4 (V-); also elsewhere on the board
~OVP_FAULT: C111.2, Q25.3 (D), R132.2; also elsewhere on the board

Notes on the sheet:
Constant Voltage (CV) and Constant Current (CC) mode detection and indication
Over-voltage protection (OVP)

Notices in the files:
parts and their libraries:
project_license: Licensed under the TAPR Open Hardware License (www.tapr.org/OHL)
